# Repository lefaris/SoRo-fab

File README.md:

# SoRo-fab: Open-Source Fabrication for Motor-Tendon Actuated Soft Robots

This repository provides a detailed, standardized fabrication methodology for creating untethered terrestrial soft robots (uTerreSoRo) with comprehensive documentation of design principles, manufacturing best practices, and performance evaluation frameworks.  This is supplementary material for the in-progress paper **An Open-Source Fabrication Strategy and Repeatability Analysis for Motor-Tendon Actuated (MTA) Soft Robots** that will be submitted soon.

---

## Overview

> **Work in Progress**: This repository is being actively developed alongside the paper submission process. Additional materials including CAD files, detailed fabrication guides, and extended documentation will be added progressively. Star/watch this repository for updates!

Soft robotics is a rapidly advancing field, but soft robots (SoRos) remain rare in everyday applications due to complexities in design and lack of consistency in fabrication techniques. Unlike rigid robots with standardized manufacturing pipelines, SoRos still lack broadly adopted methodologies and transparent reporting of fabrication practices.

This work addresses these challenges by providing:

- **Detailed fabrication methodology** for motor-tendon actuated soft robots
- **Critical design principles** including cavity optimization and bio-inspired stiffness gradients  
- **Best practices** for motor anchoring and rigid-soft integration
- **Comprehensive repeatability and reproducibility analysis** across multiple prototypes
- **Task-based performance evaluation** with statistical validation

---

## Repository Structure

```
SoRo-fab/
├── PCBs/                     # PCB designs for different iterations
│   ├── KiCAD_3limbs/         # Gerber/drill/schematic files for 3 limb SoRo
│   ├── KiCAD_4limbs/         # Gerber/drill/schematic files for 4 limb SoRo
│   └── RSC_4limb_big_mode/   # Design files for in-person large 4 limb PCB fab
├── design_files/             # CAD files of hub, hub cap, and mold + pulley (coming soon)
├── experiments/              # Experimental data and analysis scripts
│   ├── raw_data/             # Marker tracking data
│   ├── analysis/             # Python covariance confidence ellipse code
│   └── statistical_tests/    # (Coming soon) Repeatability/reproducibility analysis
├── media/                    # Images, videos, and supplementary materials
└── README.md                 # This file

Coming Soon:
├── fabrication_guide/         # Detailed step-by-step instructions
├── firmware/                  # Microcontroller code and gait sequences
└── docs/                      # Extended documentation
```

---

## Current Repository Contents

### design/
CAD files for SoRo
- Semi-flexible hub with motor mating and ziptie holes
- Hub cap for sealing with cable hole
- Battery enclosure
- Limb mold (coming soon)
- Pulley (coming soon)

### PCBs/
Custom 2-layer PCB design for the uTerreSoRo control system:
- Gerber files for manufacturing (in-person fab lab and external manufacturer)
- Schematic diagrams showing circuit design
- Board layouts
- Drill files

**Key Features**:
- Seeeduino XIAO integration
- 4x TB6643KQ motor driver support
- I2C interface for 6-axis IMU
- LiPo battery management enables tetherless capabilities
- Compact design fits in central hub

### experiments/
Experimental data and analysis code for repeatability/reproducibility evaluation:
- Gait-based twist locomotion data
- Covariance confidence ellipse script for consistency analysis

**Includes**: Data from all three independently fabricated prototypes (Blue, Black, Purple)

### media/
Visual documentation of the fabrication process and robot performance:
- Fabrication process step-by-step photos
- Completed robot prototype images
- Supplementary materials for the paper

---

## Getting Started

### Prerequisites

**Materials**
- Dragon Skin Silicone Rubber (30A shore hardness) for limbs
- NinjaFlex TPU (85A shore hardness) for hub
- nGen filament for molds
- Braided fishing line (high-strength) for tendons
- PTFE tubing for tendon paths
- Two-pronged fishing hooks for tendon anchoring

**Equipment**
- 3D printer
- Vacuum chamber
- Power drill with mixing attachment
- Mold release agent
- Scale (accurate to 1g)
- Zip ties and pliers

**Electronics** 
- Seeeduino XIAO microcontroller
- 4x Maxon DC motors
- 4x TB6643KQ full-bridge motor drivers
- 5V voltage regulator
- IRF510 power MOSFET
- shunt regulator
- buzzer
- resistors
- JST connectors
- 11.4V 1.1Ah LiPo battery (3-cell)
- Custom PCB

### Installation

1. **Clone the repository**
   ```bash
   git clone https://github.com/lefaris/SoRo-fab.git
   cd SoRo-fab
   ```

2. **Explore existing materials**
   - PCB designs are in `PCBs/`
   - Hub files are in `design/`
   - Experimental data and analysis scripts in `experiments/`
   - Images and videos in `media/`

3. **Coming soon**
   - CAD files for molds
   - Detailed fabrication guide with photos
   - Firmware and control code
   - Extended documentation

**Note**: This repository is actively being developed. Additional materials including fabrication guides and firmware will be added as the paper progresses through review.

---

## Citation

If you use this fabrication methodology in your research, please cite (coming soon)

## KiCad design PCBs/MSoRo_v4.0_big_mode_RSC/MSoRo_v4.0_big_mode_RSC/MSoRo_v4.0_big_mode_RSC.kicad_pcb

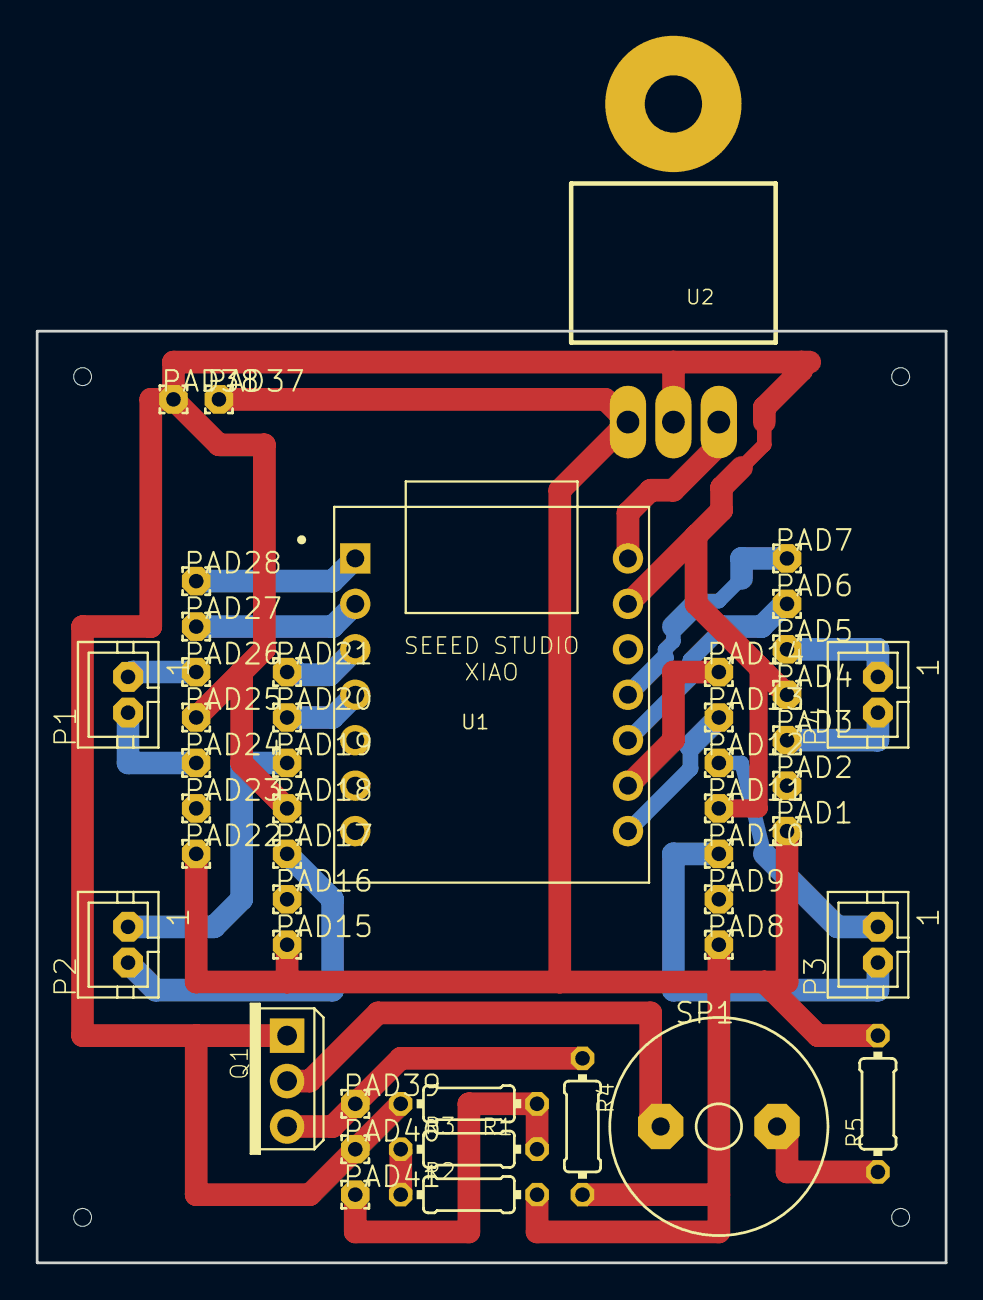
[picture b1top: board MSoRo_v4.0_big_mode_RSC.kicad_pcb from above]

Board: 16 copper layers, 50.8 x 52.1 mm, 50 parts (0 on the bottom side), 24 nets.

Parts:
@HOLE0, @HOLE1, @HOLE2, @HOLE3: (no value)
P1, P2, P3, P4: JST-PH2
PAD1, PAD2, PAD3, PAD4, PAD5, PAD6, PAD7, PAD8, PAD9, PAD10, PAD11, PAD12, PAD13, PAD14, PAD15, PAD16, PAD17, PAD18, PAD19, PAD20, PAD21, PAD22, PAD23, PAD24, PAD25, PAD26, PAD27, PAD28, PAD37, PAD38, PAD39, PAD40, PAD41: 1,6_0,8
Q1: IRF510; TO220_ALT
R1: 2.55k; 0204_7
R2, R3: 3.4k; 0204_7
R4: 470; 0204_7
R5: 150; 0204_7
SP1: AL60P
U1: XIAO-THRUHOLE; XIAO-GENERIC-THRUHOLE-MODULE14P-2.54-21X17.8MM
U2: TO-220

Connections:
BPOS: R5.1, SP1.2
DRAIN: Q1.2, SP1.1
GND: PAD4.1, PAD11.1, PAD18.1, PAD25.1, PAD38.1, PAD40.1, Q1.1, R1.2, U1.13, U2.2, U2.HEAT
GNDM1: P1.1, PAD26.1
GNDM2: P2.1, PAD19.1
GNDM3: P3.1, PAD12.1
GNDM4: P4.1, PAD5.1
IN1: PAD28.1, U1.1
IN2: PAD27.1, U1.2
IN3: PAD21.1, U1.3
IN4: PAD20.1, U1.4
IN5: PAD14.1, U1.9
IN6: PAD13.1, U1.8
IN7: PAD7.1, U1.11
IN8: PAD6.1, U1.10
REFV: PAD41.1, R1.1, R3.2
SERIES: R2.1, R3.1
VCC: PAD1.1, PAD8.1, PAD15.1, PAD22.1, PAD37.1, R2.2, R4.2, R5.2, U2.1
VCC5V: U1.14, U2.3
VCCM1: P1.2, PAD24.1
VCCM2: P2.2, PAD17.1
VCCM3: P3.2, PAD10.1
VCCM4: P4.2, PAD3.1
VOUT: PAD39.1, Q1.3, R4.1

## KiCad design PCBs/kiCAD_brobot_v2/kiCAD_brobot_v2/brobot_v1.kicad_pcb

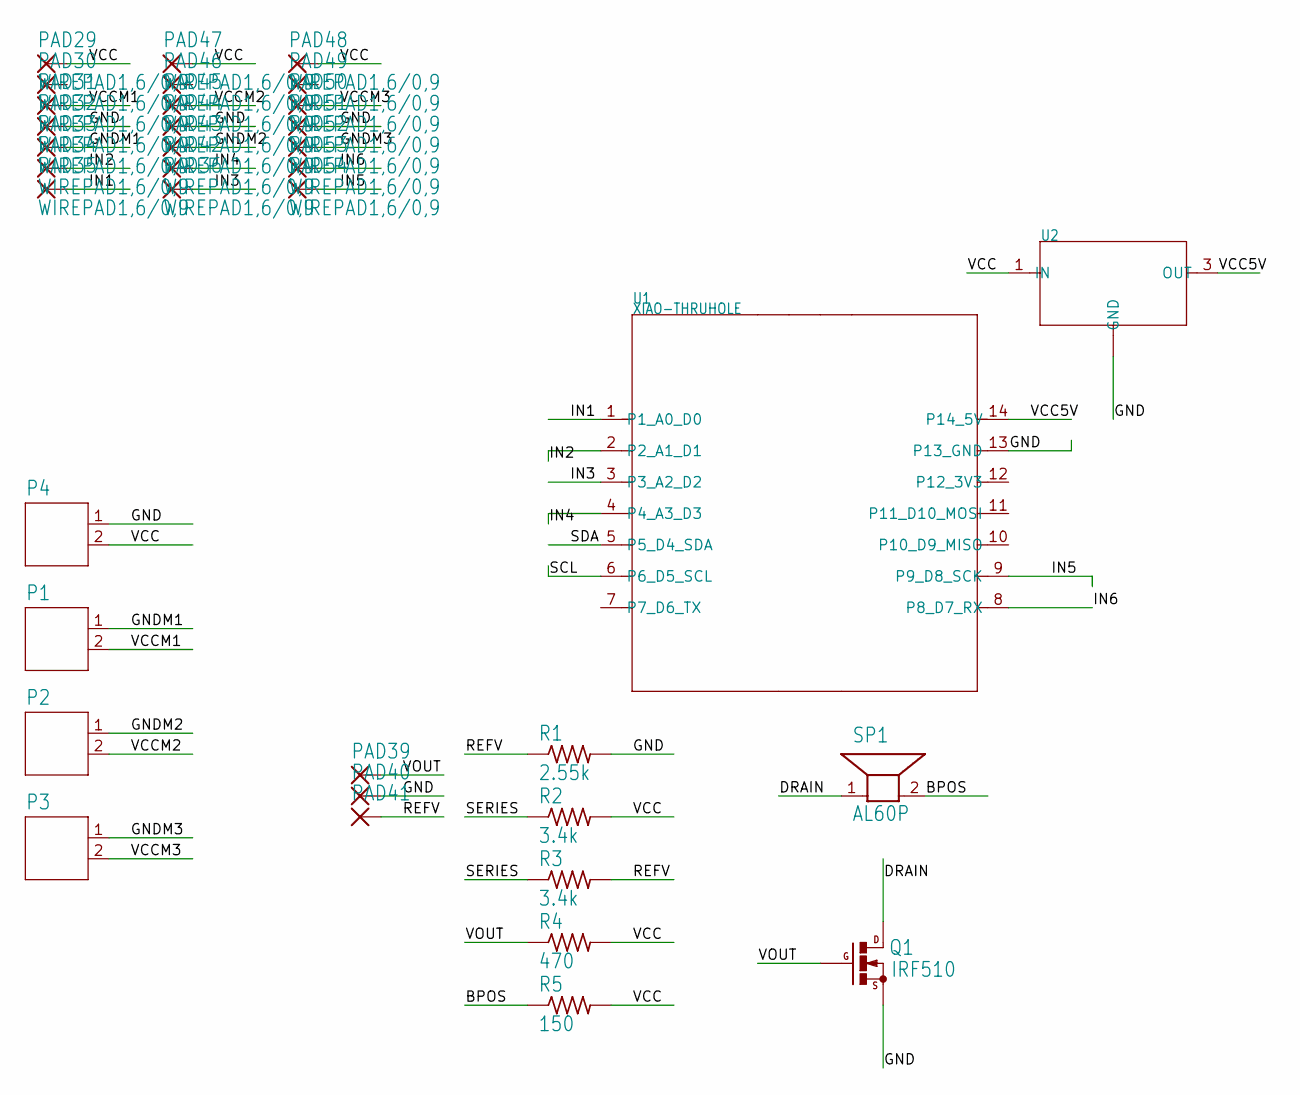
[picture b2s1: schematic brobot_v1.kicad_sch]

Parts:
P1, P2, P3, P4: JST-PH2
PAD29, PAD30, PAD31, PAD32, PAD33, PAD34, PAD35, PAD36, PAD42, PAD43, PAD44, PAD45, PAD46, PAD47, PAD48, PAD49, PAD50, PAD51, PAD52, PAD53, PAD54: WIREPAD1,6/0,9; 1,6_0,9
PAD39, PAD40, PAD41: 1,6/0,8; 1,6_0,8
Q1: IRF510; TO220_ALT
R1: 2.55k; 0204_7
R2, R3: 3.4k; 0204_7
R4: 470; 0204_7
R5: 150; 0204_7
SP1: AL60P
U1: XIAO-THRUHOLE; XIAO-GENERIC-THRUHOLE-MODULE14P-2.54-21X17.8MM
U2: PMIC-ST-L7805CV(TO-220); TO-220

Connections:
BPOS: R5.1, SP1.2
DRAIN: Q1.2 (D), SP1.1
GND: P4.1, PAD32.1, PAD40.1, PAD44.1, PAD51.1, Q1.1 (S), R1.2, U1.13 (P13_GND), U2.2 (GND), U2.HEAT (GND)
GNDM1: P1.1, PAD33.1
GNDM2: P2.1, PAD43.1
GNDM3: P3.1, PAD52.1
IN1: PAD35.1, U1.1 (P1_A0_D0)
IN2: PAD34.1, U1.2 (P2_A1_D1)
IN3: PAD36.1, U1.3 (P3_A2_D2)
IN4: PAD42.1, U1.4 (P4_A3_D3)
IN5: PAD54.1, U1.9 (P9_D8_SCK)
IN6: PAD53.1, U1.8 (P8_D7_RX)
REFV: PAD41.1, R1.1, R3.2
SCL: U1.6 (P6_D5_SCL)
SDA: U1.5 (P5_D4_SDA)
SERIES: R2.1, R3.1
VCC: P4.2, PAD29.1, PAD47.1, PAD48.1, R2.2, R4.2, R5.2, U2.1 (IN)
VCC5V: U1.14 (P14_5V), U2.3 (OUT)
VCCM1: P1.2, PAD31.1
VCCM2: P2.2, PAD45.1
VCCM3: P3.2, PAD50.1
VOUT: PAD39.1, Q1.3 (G), R4.1

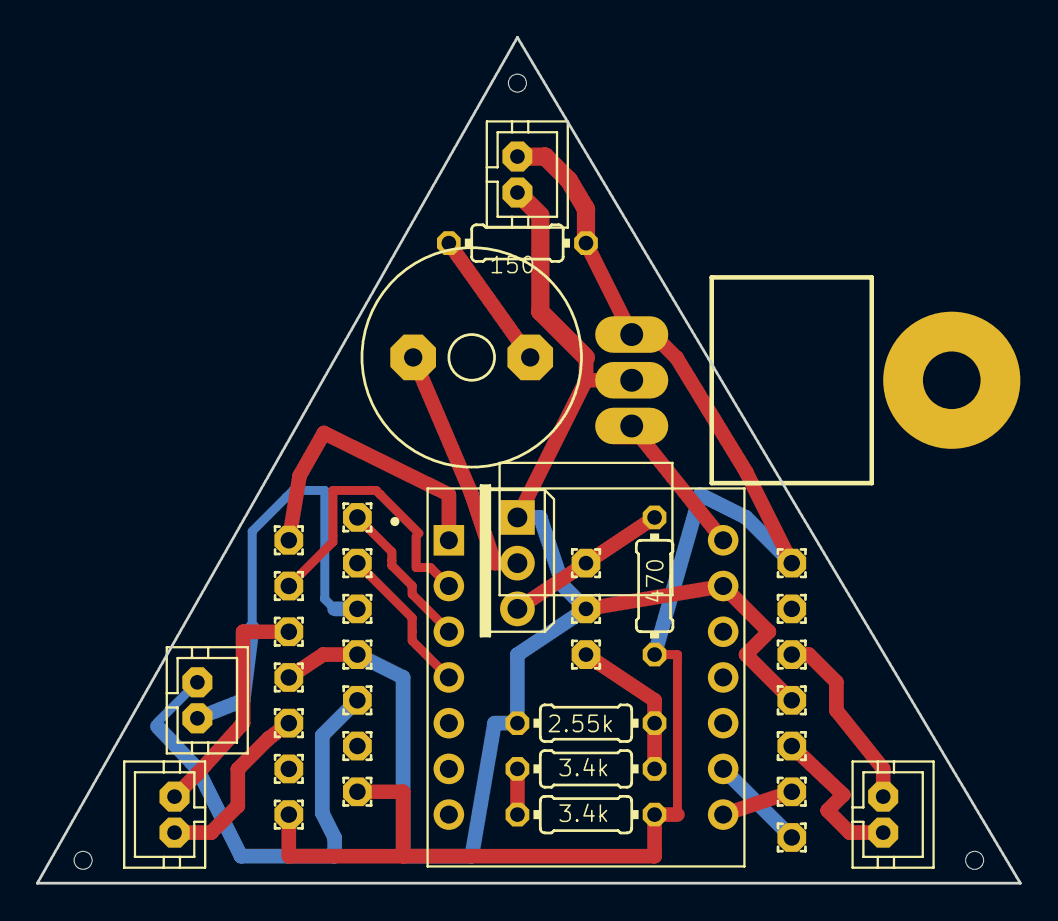
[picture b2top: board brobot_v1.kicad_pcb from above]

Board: 16 copper layers, 54.6 x 47.0 mm, 40 parts (0 on the bottom side), 20 nets.

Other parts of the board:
@HOLE0, @HOLE1, @HOLE2: (no value)

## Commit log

2026-02-13 added PCBs and figures
